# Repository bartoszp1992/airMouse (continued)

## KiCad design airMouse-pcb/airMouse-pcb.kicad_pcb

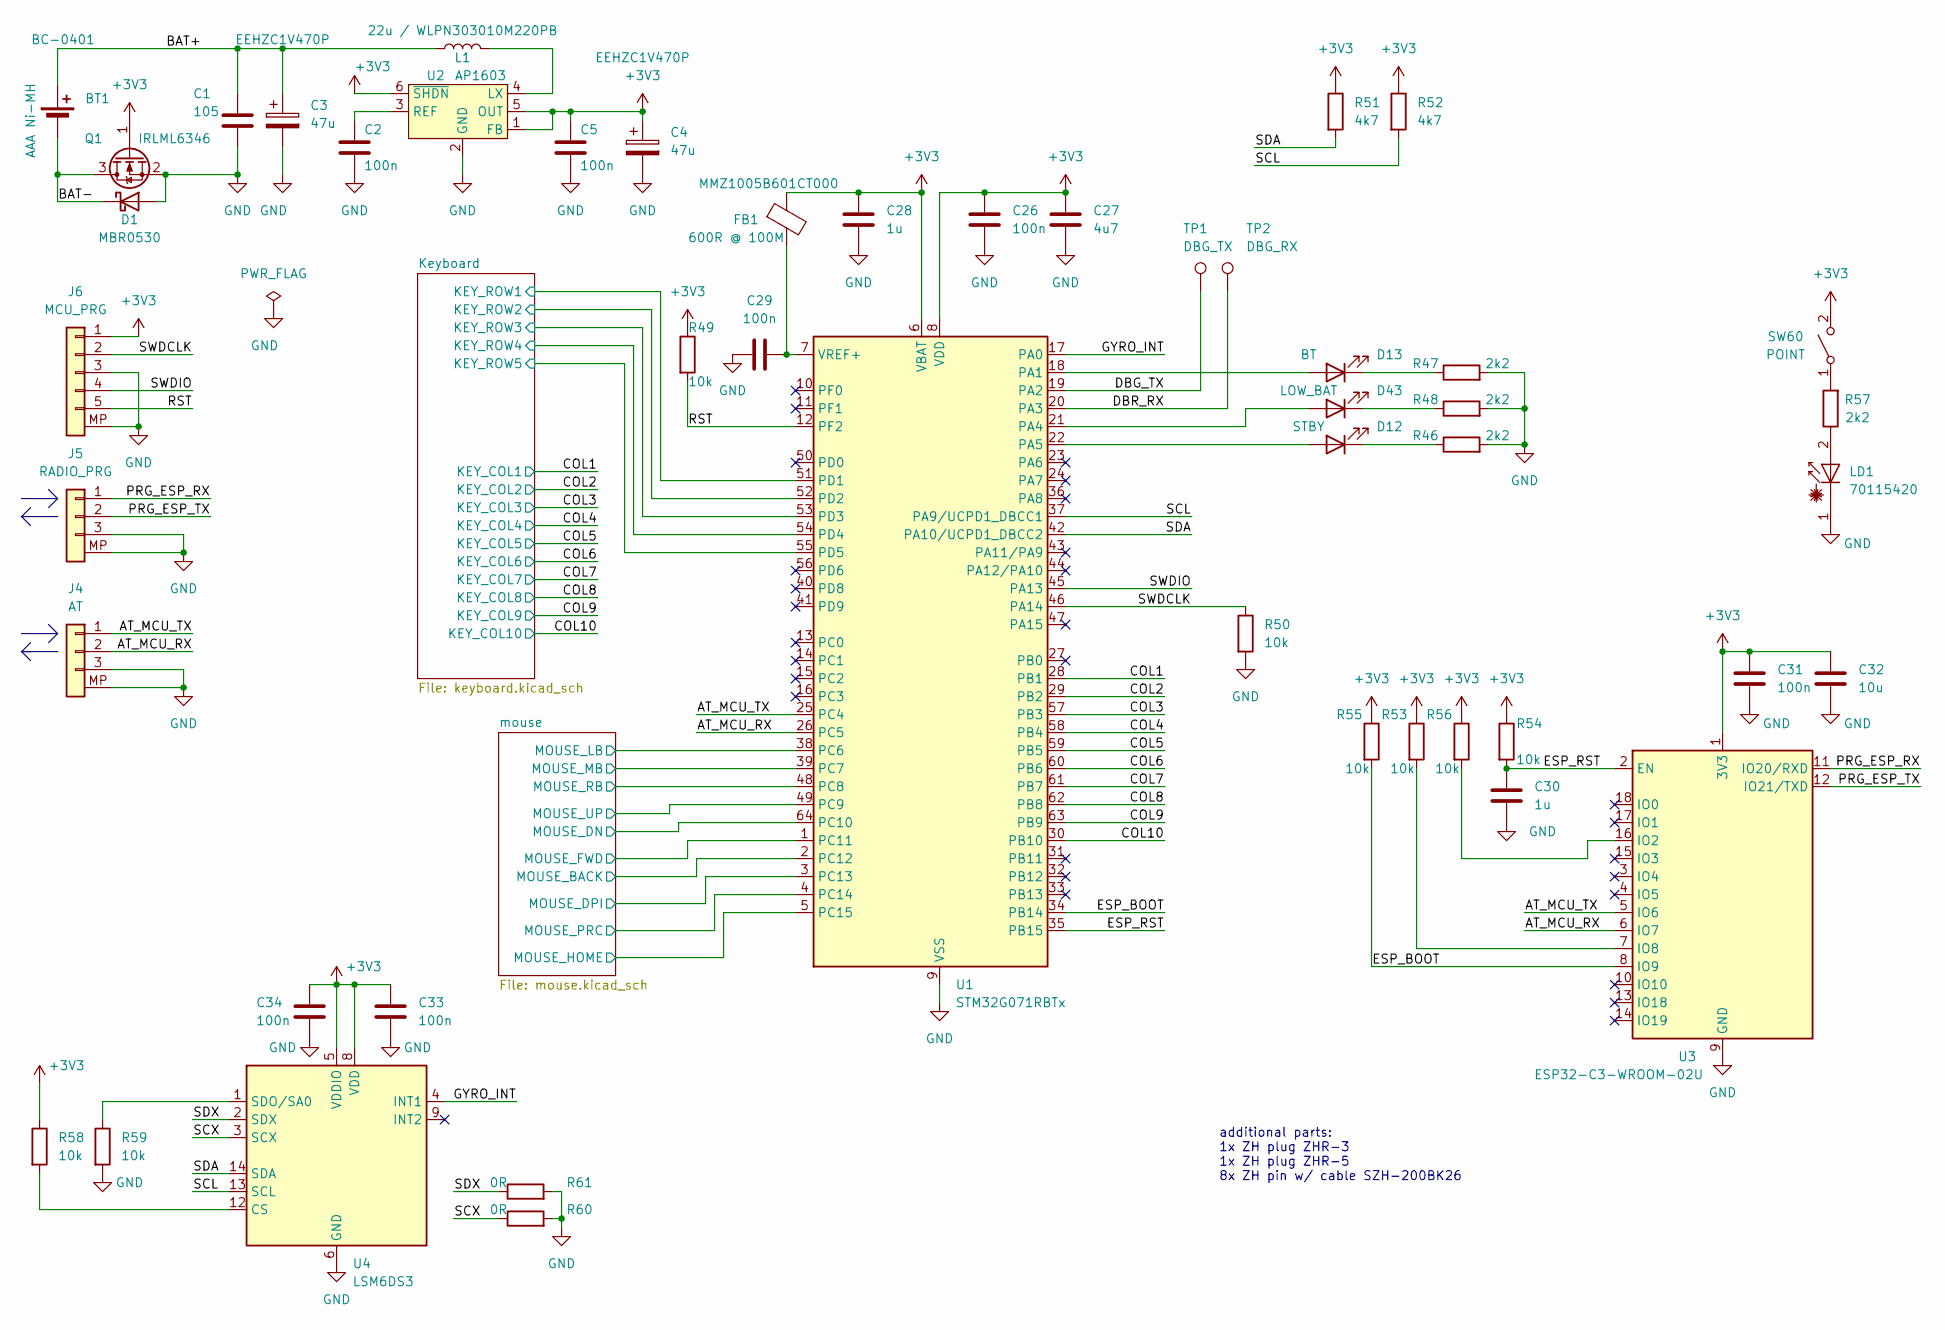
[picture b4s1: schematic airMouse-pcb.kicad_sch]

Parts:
BT1: BC-0401
C1: 105; C_0603_1608Metric
C2, C5, C26, C29, C31, C33, C34: 100n; C_0603_1608Metric
C3, C4: 47u; CP_Elec_6.3x5.8
C27: 4u7; C_0805_2012Metric
C28, C30: 1u; C_0603_1608Metric
C32: 10u; C_0805_2012Metric
D1: MBR0530; D_SOD-123
D12: STBY; LED_0603_1608Metric
D13: BT; LED_0603_1608Metric
D43: LOW_BAT; LED_0603_1608Metric
FB1: 600R @ 100M; C_0603_1608Metric
J4: AT; JST_ZH_S3B-ZR-SM4A-TF_1x03-1MP_P1.50mm_Horizontal
J5: RADIO_PRG; JST_ZH_S3B-ZR-SM4A-TF_1x03-1MP_P1.50mm_Horizontal
J6: MCU_PRG; JST_ZH_S5B-ZR-SM4A-TF_1x05-1MP_P1.50mm_Horizontal
L1: 22u / WLPN303010M220PB; L_Abracon_ASPI-3012S
LD1: 70115420; PinHeader_1x02_P2.54mm_Vertical
Q1: IRLML6346; SOT-23
R46, R47, R48, R57: 2k2; R_0603_1608Metric
R49, R50, R53, R54, R55, R56, R58, R59: 10k; R_0603_1608Metric
R51, R52: 4k7; R_0603_1608Metric
R60, R61: 0R; R_0603_1608Metric
SW60: KEY; TL3315NF100Q
TP1: DBG_TX; TestPoint_Pad_D1.0mm
TP2: DBG_RX; TestPoint_Pad_D1.0mm
U1: STM32G071RBTx; LQFP-64_10x10mm_P0.5mm
U2: AP1603; SOT-23-6
U3: ESP32-C3-WROOM-02U
U4: LSM6DS3; LGA-14_3x2.5mm_P0.5mm_LayoutBorder3x4y

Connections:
+3V3: C4.1, C5.1, C26.1, C27.1, C28.1, C31.1, C32.1, C33.1, C34.1, FB1.1, J6.1, Q1.1 (G), R49.1, R51.1, R52.1, R53.1, R54.1, R55.1, R56.1, R58.1, SW60.2 (B), U1.6 (VBAT), U1.8 (VDD), U2.1 (FB), U2.5 (OUT), U2.6 (~SHDN), U3.1 (3V3), U4.5 (VDDIO), U4.8 (VDD); also elsewhere on the board
/AT_MCU_RX: J4.2, U1.26 (PC5), U3.6 (IO7)
/AT_MCU_TX: J4.1, U1.25 (PC4), U3.5 (IO6)
/BAT+: BT1.1 (+), C1.1, C3.1, L1.1
/BAT-: BT1.2 (-), D1.1 (K), Q1.3 (D)
/COL1: U1.28 (PB1); also elsewhere on the board
/COL2: U1.29 (PB2); also elsewhere on the board
/COL3: U1.57 (PB3); also elsewhere on the board
/COL4: U1.58 (PB4); also elsewhere on the board
/COL5: U1.59 (PB5); also elsewhere on the board
/COL6: U1.60 (PB6); also elsewhere on the board
/COL7: U1.61 (PB7); also elsewhere on the board
/COL8: U1.62 (PB8); also elsewhere on the board
/COL9: U1.63 (PB9); also elsewhere on the board
/COL10: U1.30 (PB10); also elsewhere on the board
/DBG_TX: TP1.1, U1.19 (PA2)
/DBR_RX: TP2.1, U1.20 (PA3)
/ESP_BOOT: R55.2, U1.34 (PB14), U3.8 (IO9)
/ESP_RST: C30.1, R54.2, U1.35 (PB15), U3.2 (EN)
/GYRO_INT: U1.17 (PA0), U4.4 (INT1)
/Keyboard/KEY_ROW1: U1.51 (PD1); also elsewhere on the board
/Keyboard/KEY_ROW2: U1.52 (PD2); also elsewhere on the board
/Keyboard/KEY_ROW3: U1.53 (PD3); also elsewhere on the board
/Keyboard/KEY_ROW4: U1.54 (PD4); also elsewhere on the board
/Keyboard/KEY_ROW5: U1.55 (PD5); also elsewhere on the board
/PRG_ESP_RX: J5.1, U3.11 (IO20/RXD)
/PRG_ESP_TX: J5.2, U3.12 (IO21/TXD)
/RST: J6.5, R49.2, U1.12 (PF2)
/SCL: R52.2, U1.37 (PA9/UCPD1_DBCC1), U4.13 (SCL)
/SCX: R60.1, U4.3 (SCX)
/SDA: R51.2, U1.42 (PA10/UCPD1_DBCC2), U4.14 (SDA)
/SDX: R61.1, U4.2 (SDX)
/SWDCLK: J6.2, R50.1, U1.46 (PA14)
/SWDIO: J6.4, U1.45 (PA13)
/mouse/MOUSE_BACK: U1.2 (PC12); also elsewhere on the board
/mouse/MOUSE_DN: U1.64 (PC10); also elsewhere on the board
/mouse/MOUSE_DPI: U1.3 (PC13); also elsewhere on the board
/mouse/MOUSE_FWD: U1.1 (PC11); also elsewhere on the board
/mouse/MOUSE_HOME: U1.5 (PC15); also elsewhere on the board
/mouse/MOUSE_LB: U1.38 (PC6); also elsewhere on the board
/mouse/MOUSE_MB: U1.39 (PC7); also elsewhere on the board
/mouse/MOUSE_PRC: U1.4 (PC14); also elsewhere on the board
/mouse/MOUSE_RB: U1.48 (PC8); also elsewhere on the board
/mouse/MOUSE_UP: U1.49 (PC9); also elsewhere on the board
GND: C1.2, C2.2, C3.2, C4.2, C5.2, C26.2, C27.2, C28.2, C29.2, C30.2, C31.2, C32.2, C33.2, C34.2, D1.2 (A), J4.3, J4.MP (Pin_3), J5.3, J5.MP (Pin_3), J6.3, J6.MP (Pin_5), LD1.1 (K), Q1.2 (S), R46.2, R47.2, R48.2, R50.2, R59.2, R60.2, R61.2, U1.9 (VSS), U2.2 (GND), U3.9 (GND), U3.19 (GND), U4.6 (GND), U4.7 (GND); also elsewhere on the board
unnamed: D12.2 (A), U1.22 (PA5)
unnamed: D12.1 (K), R46.1
unnamed: D13.2 (A), U1.18 (PA1)
unnamed: D13.1 (K), R47.1
unnamed: D43.2 (A), U1.21 (PA4)
unnamed: D43.1 (K), R48.1
unnamed: LD1.2 (A), R57.1
unnamed: R57.2, SW60.1 (A)
unnamed: C29.1, FB1.2, U1.7 (VREF+)
unnamed: L1.2, U2.4 (LX)
unnamed: C2.1, U2.3 (REF)
unnamed: R56.2, U3.16 (IO2)
unnamed: R53.2, U3.7 (IO8)
unnamed: R58.2, U4.12 (CS)
unnamed: R59.1, U4.1 (SDO/SA0)

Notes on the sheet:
additional parts: 1x ZH plug ZHR-3 1x ZH plug ZHR-5 8x ZH pin w/ cable SZH-200BK26

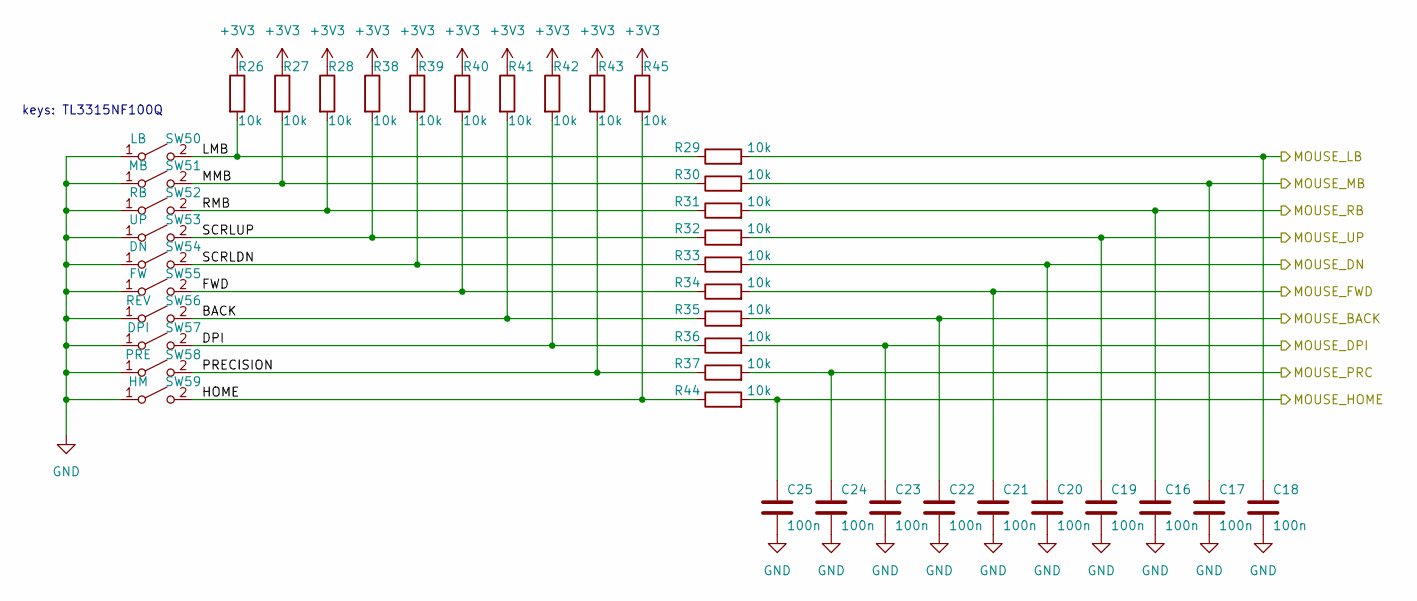
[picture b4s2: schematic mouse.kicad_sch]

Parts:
C16, C17, C18, C19, C20, C21, C22, C23, C24, C25: 100n; C_0603_1608Metric
R26, R27, R28, R29, R30, R31, R32, R33, R34, R35, R36, R37, R38, R39, R40, R41, R42, R43, R44, R45: 10k; R_0603_1608Metric
SW50, SW51, SW52, SW53, SW54, SW55, SW56, SW57, SW58, SW59: KEY; TL3315NF100Q

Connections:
+3V3: R26.1, R27.1, R28.1, R38.1, R39.1, R40.1, R41.1, R42.1, R43.1, R45.1; also elsewhere on the board
/mouse/BACK: R35.1, R41.2, SW56.2 (B)
/mouse/DPI: R36.1, R42.2, SW57.2 (B)
/mouse/FWD: R34.1, R40.2, SW55.2 (B)
/mouse/HOME: R44.1, R45.2, SW59.2 (B)
/mouse/LMB: R26.2, R29.1, SW50.2 (B)
/mouse/MMB: R27.2, R30.1, SW51.2 (B)
/mouse/MOUSE_BACK: C22.1, R35.2; also elsewhere on the board
/mouse/MOUSE_DN: C20.1, R33.2; also elsewhere on the board
/mouse/MOUSE_DPI: C23.1, R36.2; also elsewhere on the board
/mouse/MOUSE_FWD: C21.1, R34.2; also elsewhere on the board
/mouse/MOUSE_HOME: C25.1, R44.2; also elsewhere on the board
/mouse/MOUSE_LB: C18.1, R29.2; also elsewhere on the board
/mouse/MOUSE_MB: C17.1, R30.2; also elsewhere on the board
/mouse/MOUSE_PRC: C24.1, R37.2; also elsewhere on the board
/mouse/MOUSE_RB: C16.1, R31.2; also elsewhere on the board
/mouse/MOUSE_UP: C19.1, R32.2; also elsewhere on the board
/mouse/PRECISION: R37.1, R43.2, SW58.2 (B)
/mouse/RMB: R28.2, R31.1, SW52.2 (B)
/mouse/SCRLDN: R33.1, R39.2, SW54.2 (B)
/mouse/SCRLUP: R32.1, R38.2, SW53.2 (B)
GND: C16.2, C17.2, C18.2, C19.2, C20.2, C21.2, C22.2, C23.2, C24.2, C25.2, SW50.1 (A), SW51.1 (A), SW52.1 (A), SW53.1 (A), SW54.1 (A), SW55.1 (A), SW56.1 (A), SW57.1 (A), SW58.1 (A), SW59.1 (A); also elsewhere on the board

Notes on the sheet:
keys: TL3315NF100Q

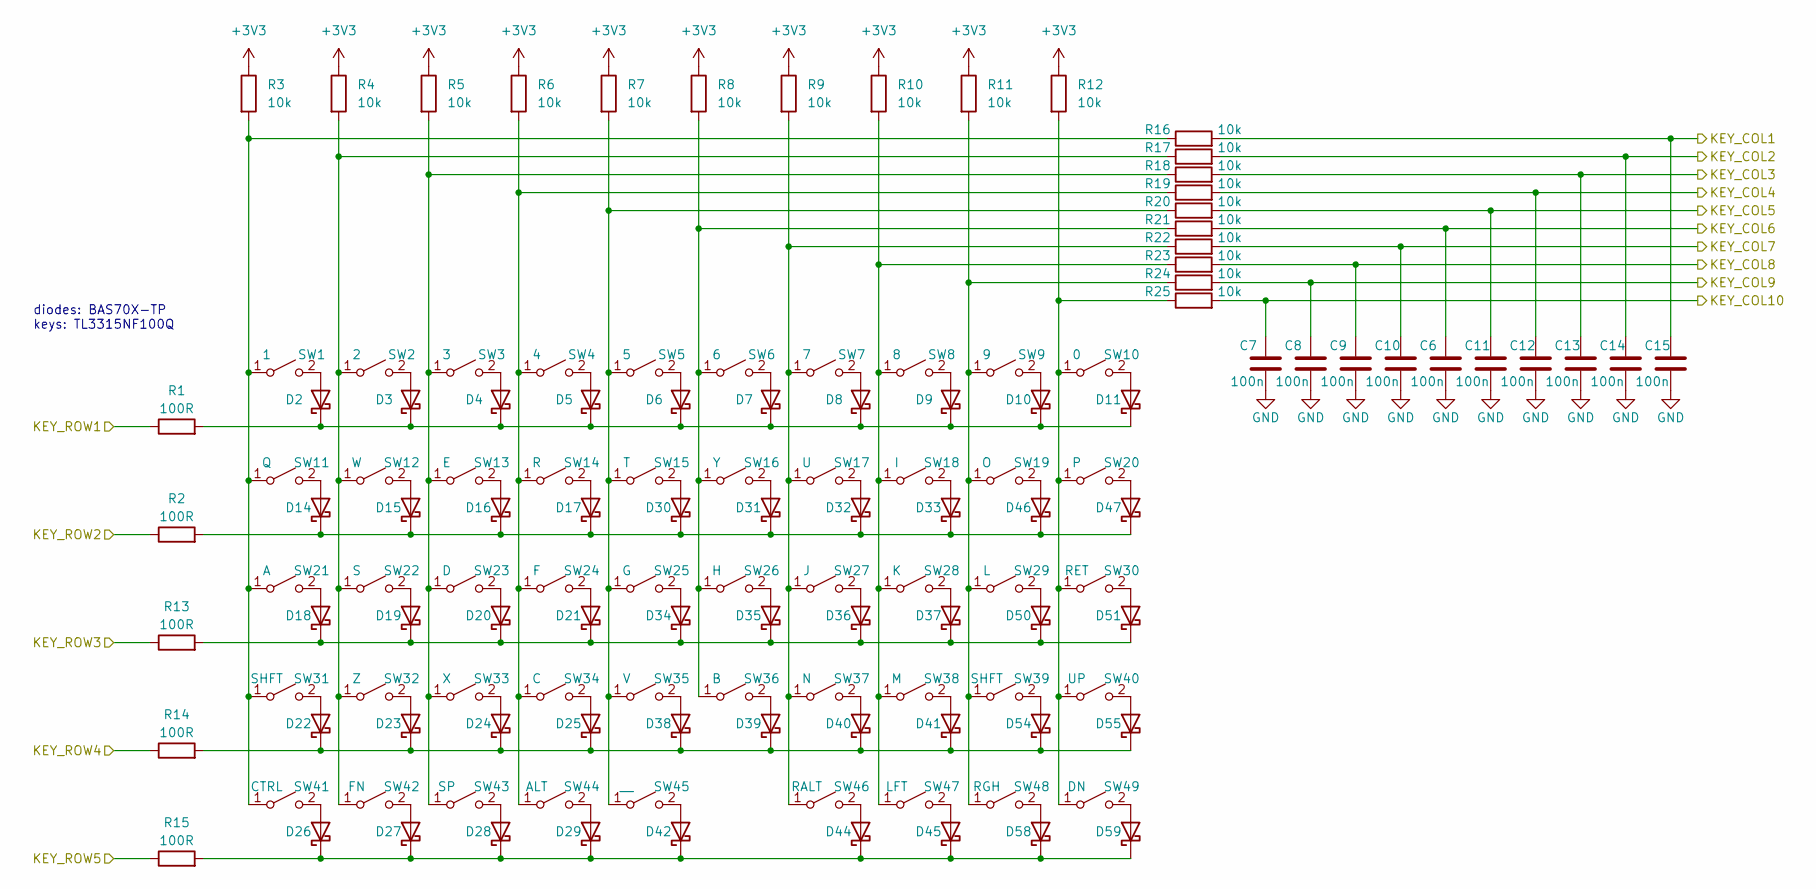
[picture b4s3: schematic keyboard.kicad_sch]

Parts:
C6, C7, C8, C9, C10, C11, C12, C13, C14, C15: 100n; C_0603_1608Metric
D2, D3, D4, D5, D6, D7, D8, D9, D10, D11, D14, D15, D16, D17, D18, D19, D20, D21, D22, D23, D24, D25, D26, D27, D28, D29, D30, D31, D32, D33, D34, D35, D36, D37, D38, D39, D40, D41, D42, D44, D45, D46, D47, D50, D51, D54, D55, D58, D59: BAS70X-TP; D_SOD-523
R1, R2, R13, R14, R15: 100R; R_0603_1608Metric
R3, R4, R5, R6, R7, R8, R9, R10, R11, R12, R16, R17, R18, R19, R20, R21, R22, R23, R24, R25: 10k; R_0603_1608Metric
SW1, SW2, SW3, SW4, SW5, SW6, SW7, SW8, SW9, SW10, SW11, SW12, SW13, SW14, SW15, SW16, SW17, SW18, SW19, SW20, SW21, SW22, SW23, SW24, SW25, SW26, SW27, SW28, SW29, SW30, SW31, SW32, SW33, SW34, SW35, SW36, SW37, SW38, SW39, SW40, SW41, SW42, SW43, SW44, SW45, SW46, SW47, SW48, SW49: KEY; TL3315NF100Q

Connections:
+3V3: R3.1, R4.1, R5.1, R6.1, R7.1, R8.1, R9.1, R10.1, R11.1, R12.1; also elsewhere on the board
/COL1: C15.1, R16.2; also elsewhere on the board
/COL2: C14.1, R17.2; also elsewhere on the board
/COL3: C13.1, R18.2; also elsewhere on the board
/COL4: C12.1, R19.2; also elsewhere on the board
/COL5: C11.1, R20.2; also elsewhere on the board
/COL6: C6.1, R21.2; also elsewhere on the board
/COL7: C10.1, R22.2; also elsewhere on the board
/COL8: C9.1, R23.2; also elsewhere on the board
/COL9: C8.1, R24.2; also elsewhere on the board
/COL10: C7.1, R25.2; also elsewhere on the board
/Keyboard/KEY_ROW1: R1.1; also elsewhere on the board
/Keyboard/KEY_ROW2: R2.1; also elsewhere on the board
/Keyboard/KEY_ROW3: R13.1; also elsewhere on the board
/Keyboard/KEY_ROW4: R14.1; also elsewhere on the board
/Keyboard/KEY_ROW5: R15.1; also elsewhere on the board
GND: C6.2, C7.2, C8.2, C9.2, C10.2, C11.2, C12.2, C13.2, C14.2, C15.2; also elsewhere on the board
unnamed: D2.2 (A), SW1.2 (B)
unnamed: D3.2 (A), SW2.2 (B)
unnamed: D4.2 (A), SW3.2 (B)
unnamed: D5.2 (A), SW4.2 (B)
unnamed: D6.2 (A), SW5.2 (B)
unnamed: D7.2 (A), SW6.2 (B)
unnamed: D8.2 (A), SW7.2 (B)
unnamed: D9.2 (A), SW8.2 (B)
unnamed: D10.2 (A), SW9.2 (B)
unnamed: D2.1 (K), D3.1 (K), D4.1 (K), D5.1 (K), D6.1 (K), D7.1 (K), D8.1 (K), D9.1 (K), D10.1 (K), D11.1 (K), R1.2
unnamed: D11.2 (A), SW10.2 (B)
unnamed: D14.2 (A), SW11.2 (B)
unnamed: D14.1 (K), D15.1 (K), D16.1 (K), D17.1 (K), D30.1 (K), D31.1 (K), D32.1 (K), D33.1 (K), D46.1 (K), D47.1 (K), R2.2
unnamed: D15.2 (A), SW12.2 (B)
unnamed: D16.2 (A), SW13.2 (B)
unnamed: D17.2 (A), SW14.2 (B)
unnamed: D18.2 (A), SW21.2 (B)
unnamed: D18.1 (K), D19.1 (K), D20.1 (K), D21.1 (K), D34.1 (K), D35.1 (K), D36.1 (K), D37.1 (K), D50.1 (K), D51.1 (K), R13.2
unnamed: D19.2 (A), SW22.2 (B)
unnamed: D20.2 (A), SW23.2 (B)
unnamed: D21.2 (A), SW24.2 (B)
unnamed: D22.2 (A), SW31.2 (B)
unnamed: D22.1 (K), D23.1 (K), D24.1 (K), D25.1 (K), D38.1 (K), D39.1 (K), D40.1 (K), D41.1 (K), D54.1 (K), D55.1 (K), R14.2
unnamed: D23.2 (A), SW32.2 (B)
unnamed: D24.2 (A), SW33.2 (B)
unnamed: D25.2 (A), SW34.2 (B)
unnamed: D26.2 (A), SW41.2 (B)
unnamed: D26.1 (K), D27.1 (K), D28.1 (K), D29.1 (K), D42.1 (K), D44.1 (K), D45.1 (K), D58.1 (K), D59.1 (K), R15.2
unnamed: D27.2 (A), SW42.2 (B)
unnamed: D28.2 (A), SW43.2 (B)
unnamed: D29.2 (A), SW44.2 (B)
unnamed: D30.2 (A), SW15.2 (B)
unnamed: D31.2 (A), SW16.2 (B)
unnamed: D32.2 (A), SW17.2 (B)
unnamed: D33.2 (A), SW18.2 (B)
unnamed: D34.2 (A), SW25.2 (B)
unnamed: D35.2 (A), SW26.2 (B)
unnamed: D36.2 (A), SW27.2 (B)
unnamed: D37.2 (A), SW28.2 (B)
unnamed: D38.2 (A), SW35.2 (B)
unnamed: D39.2 (A), SW36.2 (B)
unnamed: D40.2 (A), SW37.2 (B)
unnamed: D41.2 (A), SW38.2 (B)
unnamed: D42.2 (A), SW45.2 (B)
unnamed: D44.2 (A), SW46.2 (B)
unnamed: D45.2 (A), SW47.2 (B)
unnamed: D46.2 (A), SW19.2 (B)
unnamed: D47.2 (A), SW20.2 (B)
unnamed: D50.2 (A), SW29.2 (B)
unnamed: D51.2 (A), SW30.2 (B)
unnamed: D54.2 (A), SW39.2 (B)
unnamed: D55.2 (A), SW40.2 (B)
unnamed: D58.2 (A), SW48.2 (B)
unnamed: D59.2 (A), SW49.2 (B)
unnamed: R3.2, R16.1, SW1.1 (A), SW11.1 (A), SW21.1 (A), SW31.1 (A), SW41.1 (A)
unnamed: R12.2, R25.1, SW10.1 (A), SW20.1 (A), SW30.1 (A), SW40.1 (A), SW49.1 (A)
unnamed: R4.2, R17.1, SW2.1 (A), SW12.1 (A), SW22.1 (A), SW32.1 (A), SW42.1 (A)
unnamed: R5.2, R18.1, SW3.1 (A), SW13.1 (A), SW23.1 (A), SW33.1 (A), SW43.1 (A)
unnamed: R6.2, R19.1, SW4.1 (A), SW14.1 (A), SW24.1 (A), SW34.1 (A), SW44.1 (A)
unnamed: R7.2, R20.1, SW5.1 (A), SW15.1 (A), SW25.1 (A), SW35.1 (A), SW45.1 (A)
unnamed: R8.2, R21.1, SW6.1 (A), SW16.1 (A), SW26.1 (A), SW36.1 (A)
unnamed: R9.2, R22.1, SW7.1 (A), SW17.1 (A), SW27.1 (A), SW37.1 (A), SW46.1 (A)
unnamed: R10.2, R23.1, SW8.1 (A), SW18.1 (A), SW28.1 (A), SW38.1 (A), SW47.1 (A)
unnamed: R11.2, R24.1, SW9.1 (A), SW19.1 (A), SW29.1 (A), SW39.1 (A), SW48.1 (A)

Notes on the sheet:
diodes: BAS70X-TP keys: TL3315NF100Q

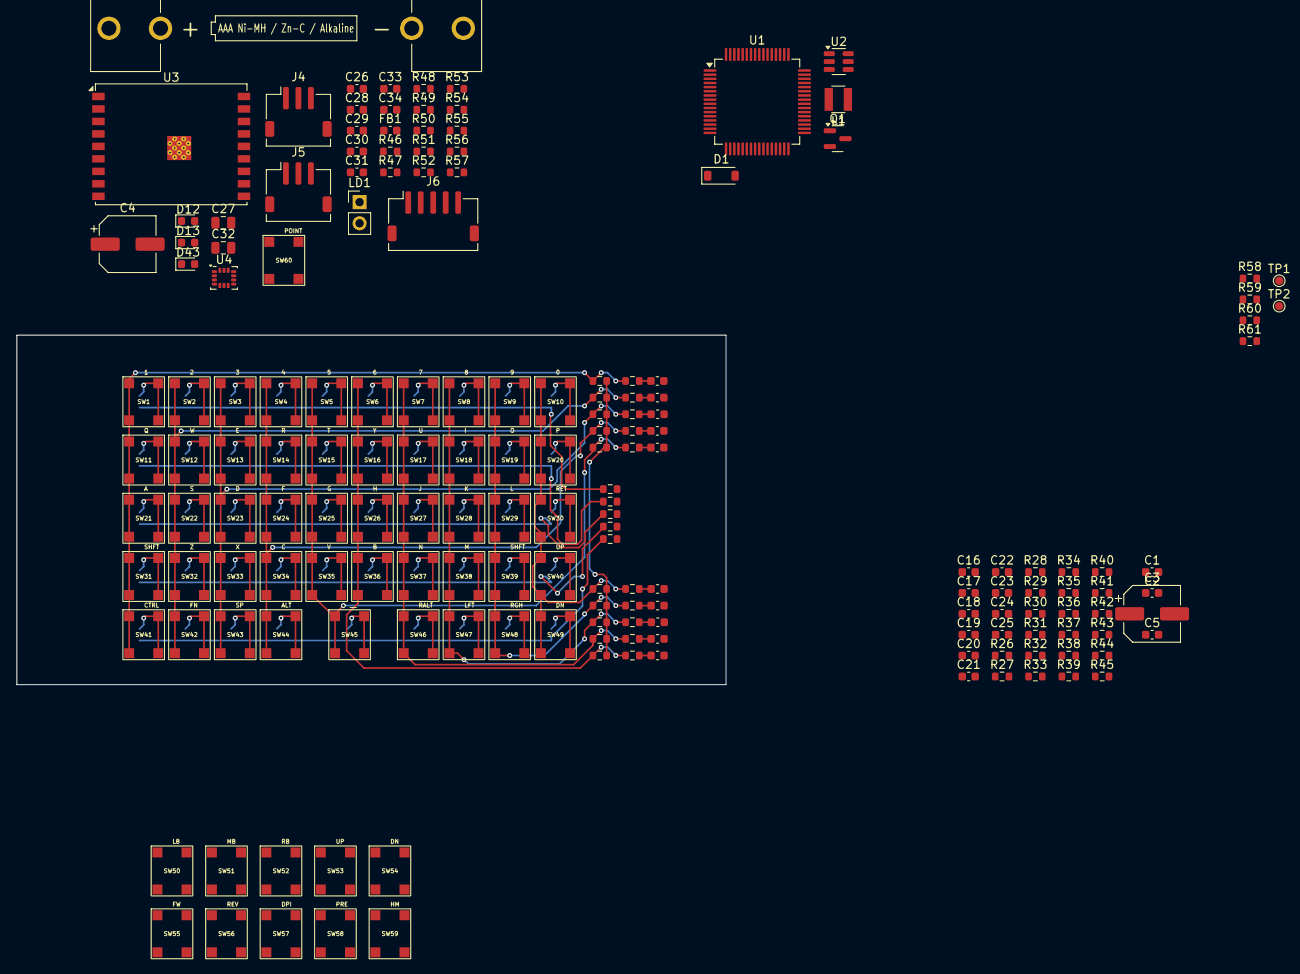
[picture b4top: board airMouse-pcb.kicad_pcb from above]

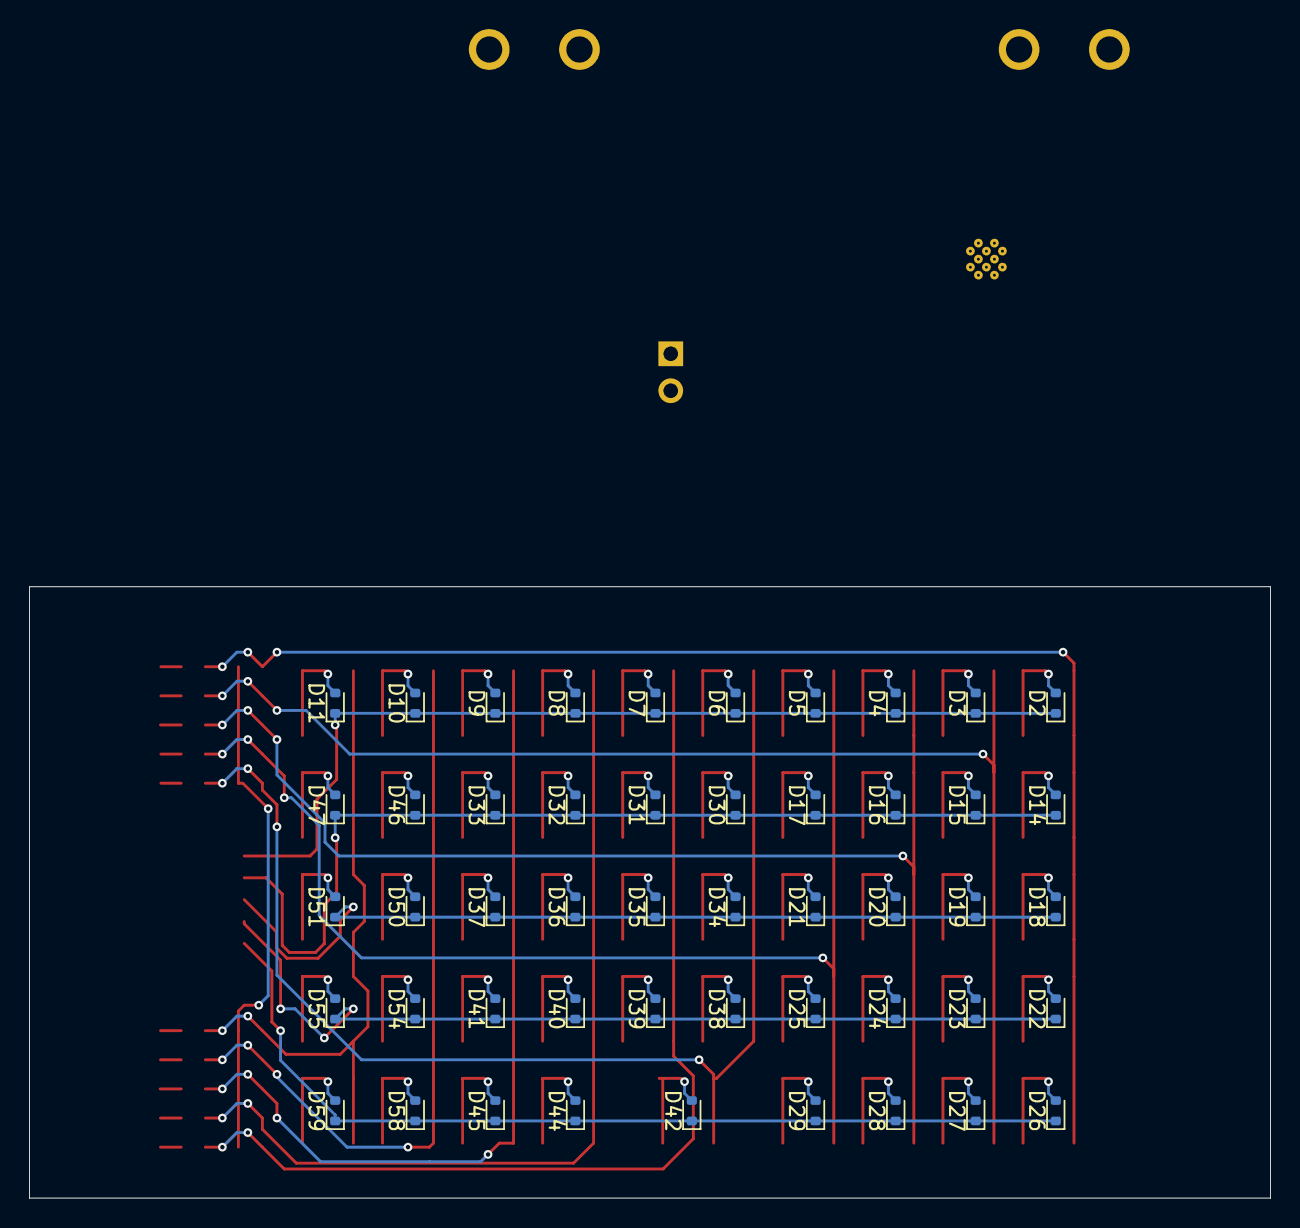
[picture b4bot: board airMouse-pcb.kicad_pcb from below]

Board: 2 copper layers, 85.2 x 42.0 mm, 222 parts (49 on the bottom side), 134 nets.

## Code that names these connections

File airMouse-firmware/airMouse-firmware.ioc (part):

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Mcu.Name=STM32G071R(6-8-B)Tx
Mcu.Package=LQFP64
Mcu.UserName=STM32G071RBTx
PA0.GPIOParameters=GPIO_PuPd,GPIO_Label
PA0.GPIO_Label=GYRO_INT
PA0.GPIO_PuPd=GPIO_NOPULL
PA0.Signal=GPXTI0
PA1.GPIOParameters=GPIO_Label
PA1.GPIO_Label=LED_BLUE
PA1.Signal=GPIO_Output
PA10.GPIOParameters=GPIO_Pu
PA10.GPIO_Pu=GPIO_NOPULL
PA10.Mode=I2C
PA10.Signal=I2C1_SDA
PA4.GPIOParameters=GPIO_Label
PA4.GPIO_Label=LED_RED
PA4.Signal=GPIO_Output
PA5.GPIOParameters=GPIO_Label
PA5.GPIO_Label=LED_GREEN
PA5.Signal=GPIO_Output
PA9.GPIOParameters=GPIO_Pu
PA9.GPIO_Pu=GPIO_NOPULL
PA9.Mode=I2C
PA9.Signal=I2C1_SCL
PB0.GPIOParameters=GPIO_Label
PB0.GPIO_Label=BAT+
PB0.Mode=IN8
PB0.Signal=ADC1_IN8
PB1.GPIOParameters=GPIO_PuPd,GPIO_Label
PB1.GPIO_Label=KBD_COL1
PB1.GPIO_PuPd=GPIO_PULLUP
PB1.Signal=GPIO_Input
PB10.GPIOParameters=GPIO_PuPd,GPIO_Label
PB10.GPIO_Label=KBD_COL10
PB10.GPIO_PuPd=GPIO_PULLUP
PB10.Signal=GPIO_Input
PB14.GPIOParameters=PinState,GPIO_PuPd,GPIO_Label,GPIO_ModeDefaultOutputPP
PB14.GPIO_Label=ESP_BOOT
PB14.GPIO_ModeDefaultOutputPP=GPIO_MODE_OUTPUT_OD
PB14.GPIO_PuPd=GPIO_NOPULL
PB14.PinState=GPIO_PIN_SET
PB14.Signal=GPIO_Output
PB15.GPIOParameters=PinState,GPIO_PuPd,GPIO_Label,GPIO_ModeDefaultOutputPP
PB15.GPIO_Label=ESP_EN
PB15.GPIO_ModeDefaultOutputPP=GPIO_MODE_OUTPUT_PP
PB15.GPIO_PuPd=GPIO_NOPULL
PB15.PinState=GPIO_PIN_RESET
PB15.Signal=GPIO_Output
PB2.GPIOParameters=GPIO_PuPd,GPIO_Label
PB2.GPIO_Label=KBD_COL2
PB2.GPIO_PuPd=GPIO_PULLUP
PB2.Signal=GPIO_Input
PB3.GPIOParameters=GPIO_PuPd,GPIO_Label
PB3.GPIO_Label=KBD_COL3
PB3.GPIO_PuPd=GPIO_PULLUP
PB3.Signal=GPIO_Input
PB4.GPIOParameters=GPIO_PuPd,GPIO_Label
PB4.GPIO_Label=KBD_COL4
PB4.GPIO_PuPd=GPIO_PULLUP
PB4.Signal=GPIO_Input
PB5.GPIOParameters=GPIO_PuPd,GPIO_Label
PB5.GPIO_Label=KBD_COL5
PB5.GPIO_PuPd=GPIO_PULLUP
PB5.Signal=GPIO_Input
PB6.GPIOParameters=GPIO_PuPd,GPIO_Label
PB6.GPIO_Label=KBD_COL6
PB6.GPIO_PuPd=GPIO_PULLUP
PB6.Signal=GPIO_Input
PB7.GPIOParameters=GPIO_PuPd,GPIO_Label
PB7.GPIO_Label=KBD_COL7
PB7.GPIO_PuPd=GPIO_PULLUP
PB7.Signal=GPIO_Input
PB8.GPIOParameters=GPIO_PuPd,GPIO_Label
PB8.GPIO_Label=KBD_COL8
PB8.GPIO_PuPd=GPIO_PULLUP
PB8.Signal=GPIO_Input
PB9.GPIOParameters=GPIO_PuPd,GPIO_Label
PB9.GPIO_Label=KBD_COL9
PB9.GPIO_PuPd=GPIO_PULLUP
PB9.Signal=GPIO_Input
PC10.GPIOParameters=GPIO_PuPd,GPIO_Label
PC10.GPIO_Label=MUS_DN
PC10.GPIO_PuPd=GPIO_PULLUP
PC10.Signal=GPIO_Input
PC11.GPIOParameters=GPIO_PuPd,GPIO_Label
PC11.GPIO_Label=MUS_PRC
PC11.GPIO_PuPd=GPIO_PULLUP
PC11.Signal=GPIO_Input
PC12.GPIOParameters=GPIO_PuPd,GPIO_Label
PC12.GPIO_Label=MUS_HOME
PC12.GPIO_PuPd=GPIO_PULLUP
PC12.Signal=GPIO_Input
PC13.GPIOParameters=GPIO_PuPd,GPIO_Label
PC13.GPIO_Label=MUS_DPI
PC13.GPIO_PuPd=GPIO_PULLUP
PC13.Signal=GPIO_Input
PC14-OSC32_IN\ (PC14).GPIOParameters=GPIO_PuPd,GPIO_Label
PC14-OSC32_IN\ (PC14).GPIO_Label=MUS_FWD
PC14-OSC32_IN\ (PC14).GPIO_PuPd=GPIO_PULLUP
PC14-OSC32_IN\ (PC14).Signal=GPIO_Input
PC15-OSC32_OUT\ (PC15).GPIOParameters=GPIO_PuPd,GPIO_Label
PC15-OSC32_OUT\ (PC15).GPIO_Label=MUS_BCK
PC15-OSC32_OUT\ (PC15).GPIO_PuPd=GPIO_PULLUP
PC15-OSC32_OUT\ (PC15).Signal=GPIO_Input
PC4.GPIOParameters=GPIO_Label
PC4.GPIO_Label=ESP_TX
PC4.Mode=Asynchronous
PC4.Signal=USART1_TX
PC5.GPIOParameters=GPIO_ModeDefaultPP,GPIO_PuPd,GPIO_Label
PC5.GPIO_Label=ESP_RX
PC5.GPIO_ModeDefaultPP=GPIO_MODE_AF_OD
PC5.GPIO_PuPd=GPIO_NOPULL
PC5.Mode=Asynchronous
PC5.Signal=USART1_RX
PC6.GPIOParameters=GPIO_PuPd,GPIO_Label,GPIO_ModeDefaultEXTI
PC6.GPIO_Label=MUS_LB
PC6.GPIO_ModeDefaultEXTI=GPIO_MODE_IT_FALLING
PC6.GPIO_PuPd=GPIO_PULLUP
PC6.Signal=GPXTI6
PC7.GPIOParameters=GPIO_PuPd,GPIO_Label
PC7.GPIO_Label=MUS_MB
PC7.GPIO_PuPd=GPIO_PULLUP
PC7.Signal=GPIO_Input
PC8.GPIOParameters=GPIO_PuPd,GPIO_Label
PC8.GPIO_Label=MUS_RB
PC8.GPIO_PuPd=GPIO_PULLUP
PC8.Signal=GPIO_Input
PC9.GPIOParameters=GPIO_PuPd,GPIO_Label
PC9.GPIO_Label=MUS_UP
PC9.GPIO_PuPd=GPIO_PULLUP
PC9.Signal=GPIO_Input
PD1.GPIOParameters=GPIO_Label
PD1.GPIO_Label=KBD_ROW1
PD1.Signal=GPIO_Output
PD2.GPIOParameters=GPIO_Label
PD2.GPIO_Label=KBD_ROW2
PD2.Signal=GPIO_Output
PD3.GPIOParameters=GPIO_Label
PD3.GPIO_Label=KBD_ROW3
PD3.Signal=GPIO_Output
PD4.GPIOParameters=GPIO_Label
PD4.GPIO_Label=KBD_ROW4
PD4.Signal=GPIO_Output
PD5.GPIOParameters=GPIO_Label
PD5.GPIO_Label=KBD_ROW5
PD5.Signal=GPIO_Output
RCC.HSE_VALUE=8000000
RCC.SYSCLKFreq_VALUE=64000000
RCC.SYSCLKSource=RCC_SYSCLKSOURCE_PLLCLK
board=custom

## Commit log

2025-02-03 initial
2025-02-03 second commit
2025-02-03 making AT command
2025-02-04 working mouse move
2025-02-05 add gyro library
2025-02-06 completed IMU library base
2025-02-08 working cursor movement
2025-02-08 faster ESP UART
2025-02-08 better move
2025-02-08 i2c variant
2025-02-08 working fast acceleration
2025-02-11 slow acceleration
2025-02-11 initial schematic
2025-02-11 key footprint
2025-02-12 add keyboard
2025-02-13 schematic
2025-02-13 add adc channel
2025-02-13 gitignore
2025-02-13 page data
2025-02-15 output for keyboard
2025-02-15 add mouse pcb
2025-02-15 thumb pcb
2025-02-15 components placed on mcu board
2025-02-15 add mcu board
2025-02-17 updated mcu board BOM with external components
2025-02-17 initializing housing
2025-02-17 adds keyboard
2025-02-18 add assembly
2025-02-18 assy1
2025-02-19 1mm thickness boards
2025-02-19 updated housing
2025-02-19 assembly
2025-02-19 placed mouse and thumb
2025-02-19 add ufl key
2025-02-19 add coil to mcu pcb
2025-02-20 add connectors 3d models
2025-02-20 pending housing
2025-02-21 better pcb models
2025-02-21 new housing concept
2025-02-21 housing pending...
2025-02-22 housing work pending
2025-02-22 add button
2025-02-22 added carbon copy sketches
2025-02-25 add tape channels
2025-02-27 add todo
2025-02-27 fixed home/prc and fwd/bck
2025-02-27 updated for kicad 9
2025-02-28 dont know, why voltage drops
2025-02-28 works with android
2025-03-01 working keyboard library
2025-03-03 refactoring...
2025-03-03 esp boot and en implemented in espat
2025-03-03 refactored
2025-03-03 created startBoost simulation
2025-03-04 fixed receiving data- overrun turned off
2025-03-05 parsing OK, ERROR and ready responses working!
2025-03-05 added not-working DMA functions to ESPAT
2025-03-07 add hid codes
2025-03-08 returning esp32 response status
2025-03-08 working on mouse buttons
2025-03-08 working on
2025-03-08 add pull mac and sendComplex functions to espat
2025-03-08 diagnosed continously pressed mouse button. If button are released, report isn't sent- becouse there's no action. So, in last report computer see that button are pressed
2025-03-10 modified gitignore
2025-03-10 remove debug and release
2025-03-10 remove release and debug
2025-03-10 refactoring
2025-03-10 bottom cover
2025-03-11 fixed housing
2025-03-11 fixed bottom base and bottom cover
2025-03-11 almost working keyboard read
2025-03-12 working qwerty keyboard
2025-03-12 improved keyboard library
2025-03-12 improved reverse functionality to keyboard library
2025-03-12 mod keys working
2025-03-12 working keyboard
2025-03-13 updated notes
2025-03-13 add polling rate counter
2025-03-13 moved ONTIME
2025-03-15 better sleep
2025-03-15 included esp-at firmware sources, and binaries fixed polling rate on linux
2025-03-15 testing low power modes
2025-03-15 acceleration and sensitivity in config
2025-03-15 small changes
2025-03-15 low power
2025-03-18 add blink library
2025-03-20 new mcu pcb
2025-03-21 new mcu-pcb
2025-03-22 working connect and disconnect
2025-03-22 add ble hid table
2025-03-24 working on BLE HID
2025-03-24 add gatts table
2025-03-31 new mcu board tests
2025-03-31 mini2 frame
2025-04-01 working on mini2
2025-04-01 new main of mini2
2025-04-02 larger buttons
2025-04-11 new mini2
